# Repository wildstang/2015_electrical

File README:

This is the 2015 electrical repository. Branched commit.

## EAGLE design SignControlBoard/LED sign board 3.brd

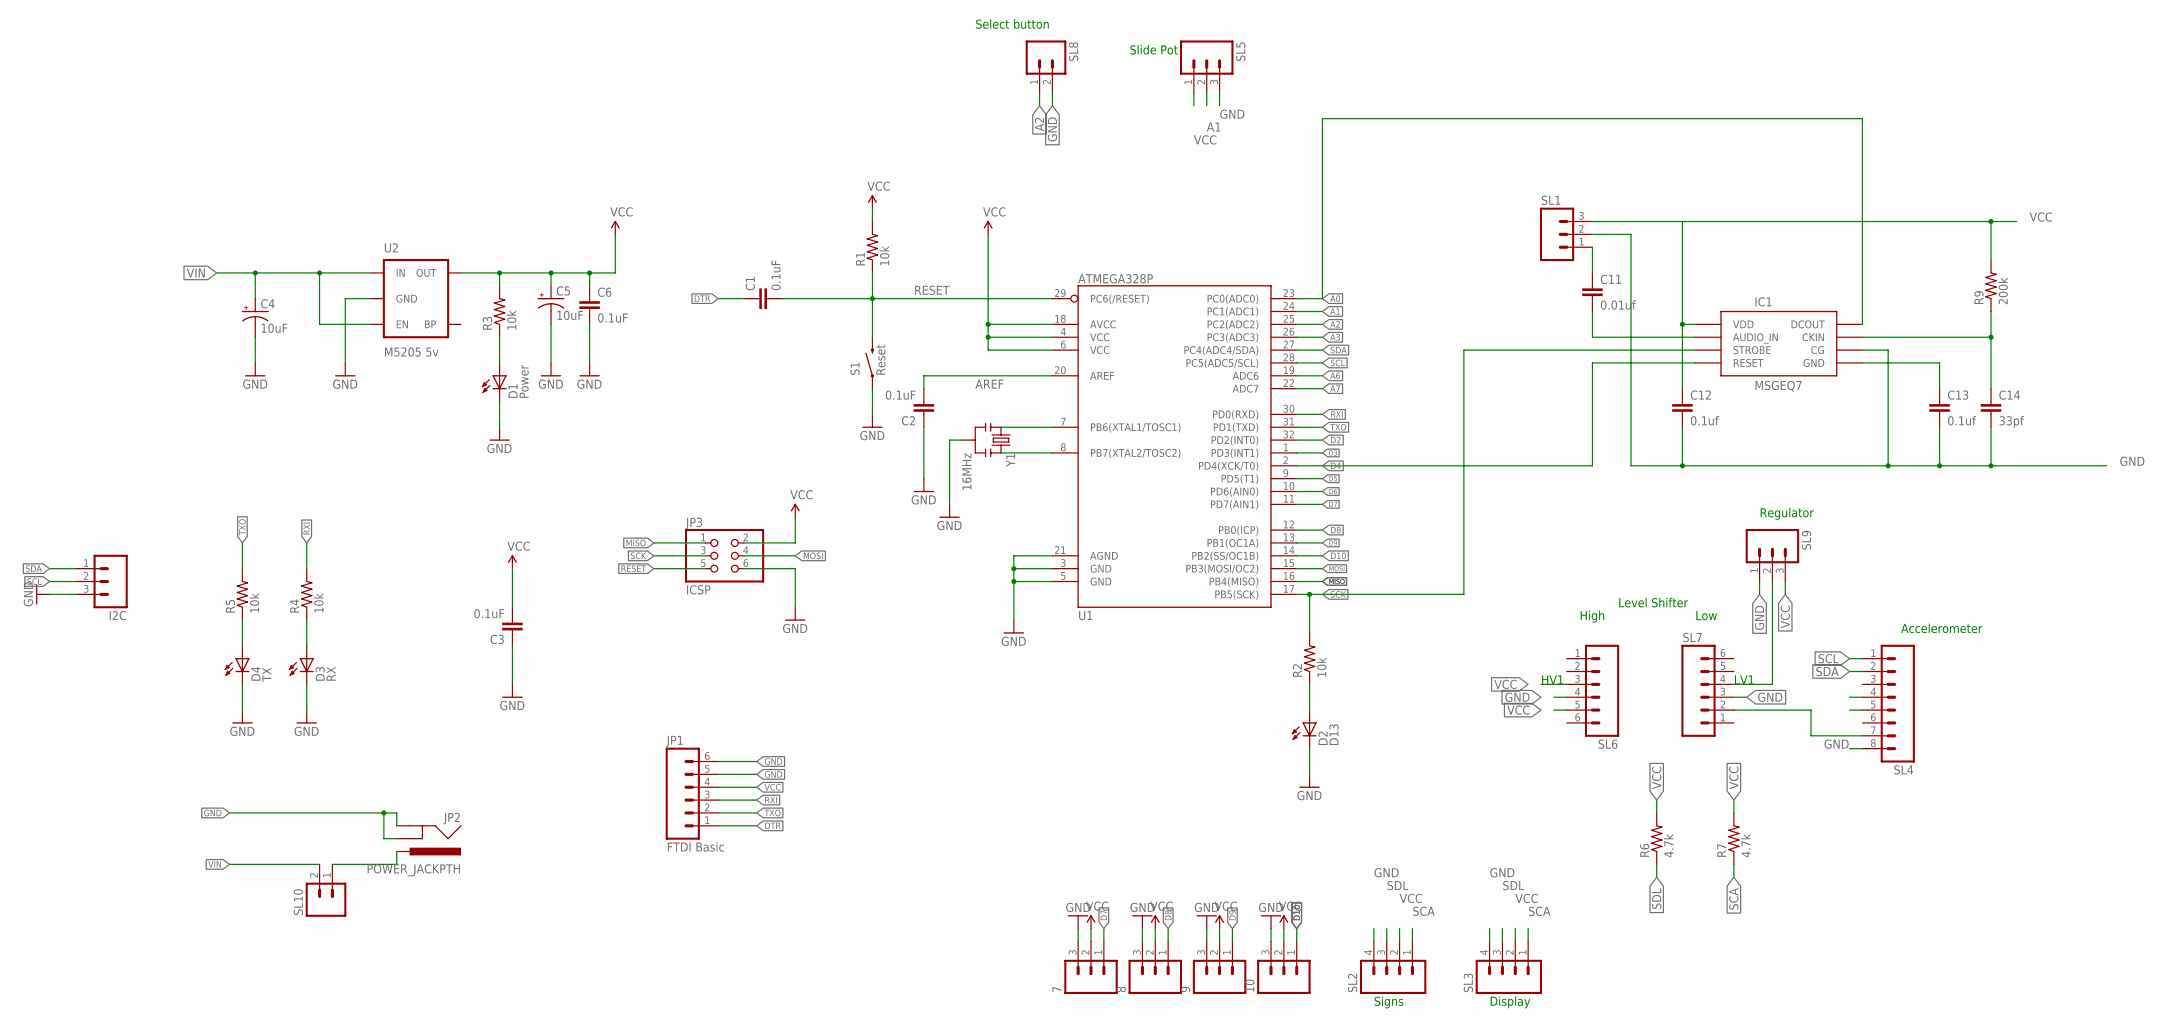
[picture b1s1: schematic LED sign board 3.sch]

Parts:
7, 8, 9, 10: M03PTH; 1X03
C1, C2, C3, C6: 0.1uF; 0603-CAP
C4, C5: 10uF; EIA3216
C11: 0.01uf; C0201
C12, C13: 0.1uf; C0201
C14: 33pf; C0201
D1: Power; LED-0603
D2: D13; LED-0603
D3: RX; LED-0603
D4: TX; LED-0603
I2C: M03PTH; 1X03
IC1: MSGEQ7DIL; DIL-08
JP1: FTDI Basic; 1X06
JP2: POWER_JACKPTH; POWER_JACK_PTH
JP3: ICSP; 2X03
R1, R2, R3, R4, R5: 10k; 0603-RES
R6, R7: 4.7k; 1206
R9: 200k; 1206
S1: Reset; TACTILE_SWITCH_SMD
SL1, SL5, SL9: M03; 03P
SL2, SL3: M04; 04P
SL4: M08; 08P
SL6, SL7: M06; 06P
SL8, SL10: M02; 02P
U1: ATMEGA328P; TQFP32-08
U2: M5205 5v; SOT23-5
Y1: 16MHz; RESONATOR-SMD

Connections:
A0: IC1.3 (DCOUT), U1.23 (PC0(ADC0))
A1: SL5.2, U1.24 (PC1(ADC1))
A2: SL8.1, U1.25 (PC2(ADC2))
A3: U1.26 (PC3(ADC3))
A6: U1.19 (ADC6)
A7: U1.22 (ADC7)
AREF: C2.2, U1.20 (AREF)
D2: U1.32 (PD2(INT0))
D3: U1.1 (PD3(INT1))
D4: IC1.7 (RESET), U1.2 (PD4(XCK/T0))
D5: U1.9 (PD5(T1))
D6: U1.10 (PD6(AIN0))
D7: 7.1, U1.11 (PD7(AIN1))
D8: 8.1, U1.12 (PB0(ICP))
D9: 9.1, U1.13 (PB1(OC1A))
D10: 10.1, U1.14 (PB2(SS/OC1B))
DTR: C1.1, JP1.1
GND: 7.3, 8.3, 9.3, 10.3, C2.1, C3.1, C4.C (-), C5.C (-), C6.2, C12.2, C13.2, C14.2, D1.C, D2.C, D3.C, D4.C, I2C.3, IC1.6 (CG), JP1.5, JP1.6, JP2.GND, JP2.GNDBREAK, JP3.6, S1.1, SL1.2, SL2.4, SL3.4, SL4.8, SL5.3, SL6.4, SL7.3, SL7.4, SL8.2, SL9.1, SL9.2, U1.3 (GND), U1.5 (GND), U1.21 (AGND), U2.2 (GND), Y1.2
MISO: JP3.1, U1.16 (PB4(MISO))
MOSI: JP3.4, U1.15 (PB3(MOSI/OC2))
unnamed: U1.7 (PB6(XTAL1/TOSC1)), Y1.1
unnamed: U1.8 (PB7(XTAL2/TOSC2)), Y1.3
unnamed: D1.A, R3.1
unnamed: D2.A, R2.1
unnamed: D3.A, R4.1
unnamed: D4.A, R5.1
unnamed: SL4.7, SL7.2
unnamed: JP2.PWR, SL10.1
unnamed: C11.1, SL1.1
unnamed: C11.2, IC1.5 (AUDIO_IN)
unnamed: C13.1, IC1.2 (GND)
unnamed: C14.1, IC1.8 (CKIN), R9.1
RESET: C1.2, JP3.5, R1.1, S1.3 (2), U1.29 (PC6(/RESET))
RXI: JP1.3, R4.2, U1.30 (PD0(RXD))
SCA: R7.1, SL2.1, SL3.1
SCK: IC1.4 (STROBE), JP3.3, R2.2, U1.17 (PB5(SCK))
SCL: I2C.2, SL4.1, U1.28 (PC5(ADC5/SCL))
SDA: I2C.1, SL4.2, U1.27 (PC4(ADC4/SDA))
SDL: R6.1, SL2.3, SL3.3
TXO: JP1.2, R5.2, U1.31 (PD1(TXD))
VCC: 7.2, 8.2, 9.2, 10.2, C3.2, C5.A (+), C6.1, C12.1, IC1.1 (VDD), JP1.4, JP3.2, R1.2, R3.2, R6.2, R7.2, R9.2, SL1.3, SL2.2, SL3.2, SL5.1, SL6.3, SL6.5, SL9.3, U1.4 (VCC), U1.6 (VCC), U1.18 (AVCC), U2.5 (OUT)
VIN: C4.A (+), SL10.2, U2.1 (IN), U2.3 (EN)

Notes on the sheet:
Accelerometer
Slide Pot
Display
Signs
Level Shifter
High
Low
Select button
Regulator
HV1
LV1

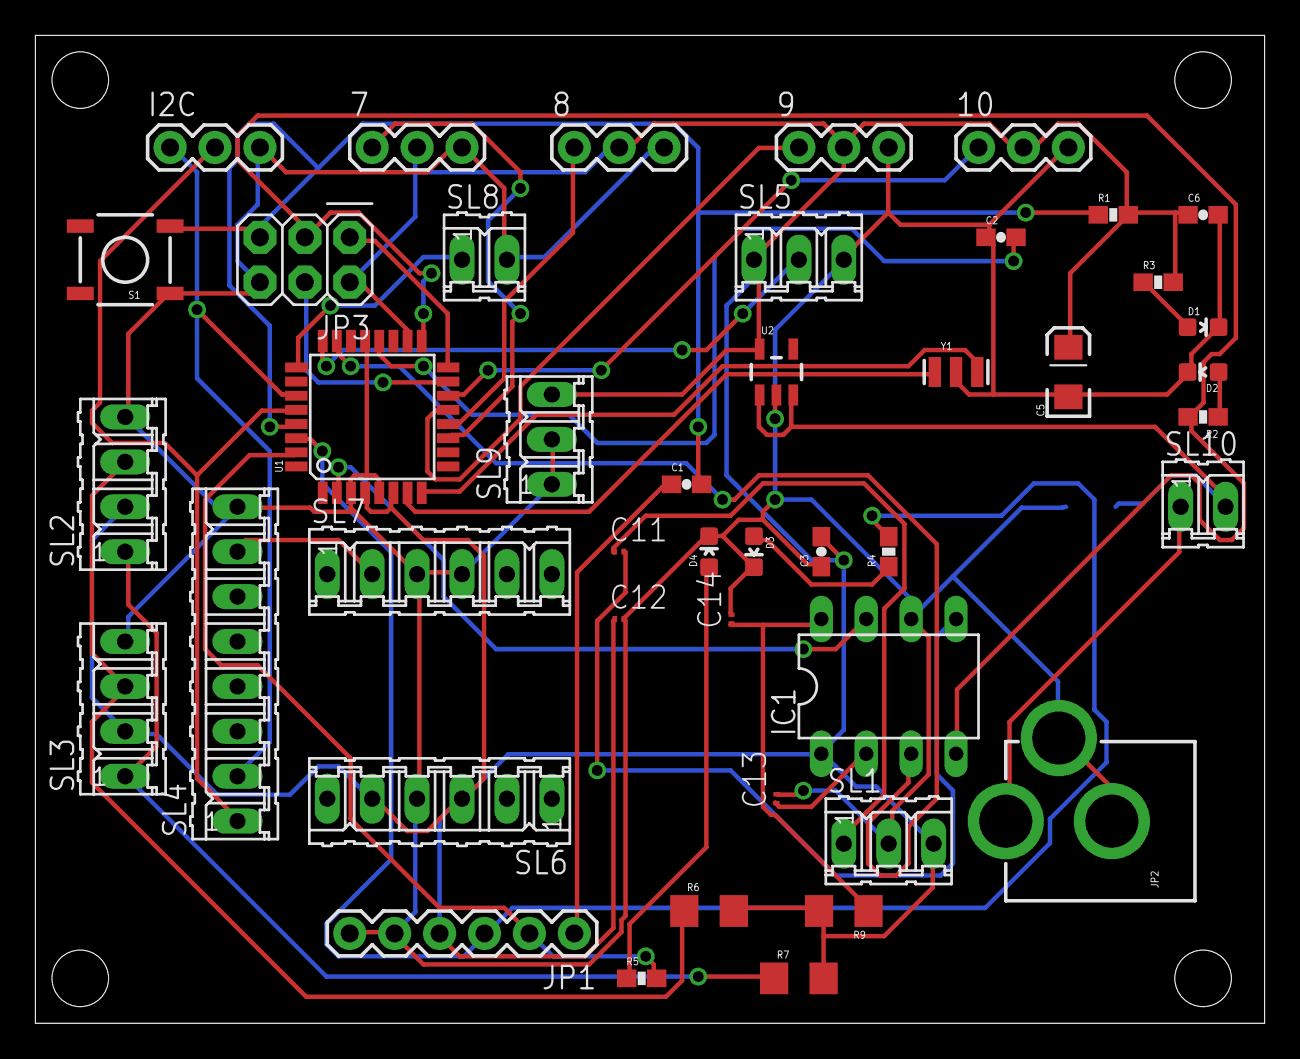
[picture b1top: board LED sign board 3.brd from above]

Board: 2 copper layers, 69.5 x 55.9 mm, 45 parts (1 on the bottom side), 35 nets.

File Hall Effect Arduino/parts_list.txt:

Partlist

Exported from Hall Effect Arduino.sch at 2/4/2015 12:22:48 PM

EAGLE Version 7.1.0 Copyright (c) 1988-2014 CadSoft

Assembly variant: 

Part     Value          Device                Package            Library                    Sheet

2                       M03PTH                1X03               SparkFun-Connectors        1
3                       M03PTH                1X03               SparkFun-Connectors        1
4                       M03PTH                1X03               SparkFun-Connectors        1
5                       M03PTH                1X03               SparkFun-Connectors        1
6                       M03PTH                1X03               SparkFun-Connectors        1
7                       M03PTH                1X03               SparkFun-Connectors        1
8                       M03PTH                1X03               SparkFun-Connectors        1
9                       M03PTH                1X03               SparkFun-Connectors        1
10                      M03PTH                1X03               SparkFun-Connectors        1
C1       0.1uF          CAP0603-CAP           0603-CAP           SparkFun-Passives          1
C2       0.1uF          CAP0603-CAP           0603-CAP           SparkFun-Passives          1
C3       0.1uF          CAP0603-CAP           0603-CAP           SparkFun-Passives          1
C4       10uF           CAP_POL1206           EIA3216            SparkFun-Passives          1
C5       10uF           CAP_POL1206           EIA3216            SparkFun-Passives          1
C6       0.1uF          CAP0603-CAP           0603-CAP           SparkFun-Passives          1
D1       Power          LED-RED0603           LED-0603           SparkFun-LED               1
D2       D13            LED-RED0603           LED-0603           SparkFun-LED               1
D3       RX             LED-GREEN0603         LED-0603           SparkFun-LED               1
D4       TX             LED-RED0603           LED-0603           SparkFun-LED               1
I2C                     M03PTH                1X03               SparkFun-Connectors        1
JP1      FTDI Basic     M06SIP                1X06               SparkFun-Connectors        1
JP3      ICSP           PINHD-2X3             2X03               SparkFun-Connectors        1
R1       10k            RESISTOR0603-RES      0603-RES           SparkFun-Passives          1
R2       10k            RESISTOR0603-RES      0603-RES           SparkFun-Passives          1
R3       10k            RESISTOR0603-RES      0603-RES           SparkFun-Passives          1
R4       10k            RESISTOR0603-RES      0603-RES           SparkFun-Passives          1
R5       10k            RESISTOR0603-RES      0603-RES           SparkFun-Passives          1
S1       Reset          SWITCH-MOMENTARY-2SMD TACTILE_SWITCH_SMD SparkFun-Electromechanical 1
U$1      LSF-SMT        LSF-SMT               LSF-SMT            LSF-SMT                    1
U1       ATMEGA328P     ATMEGA328_SMT         TQFP32-08          SparkFun-DigitalIC         1
U2       M5205 5v       MIC52055V             SOT23-5            SparkFun-PowerIC           1
Y1       16MHz          RESONATOR16MHZ        RESONATOR-SMD      SparkFun-FreqCtrl          1

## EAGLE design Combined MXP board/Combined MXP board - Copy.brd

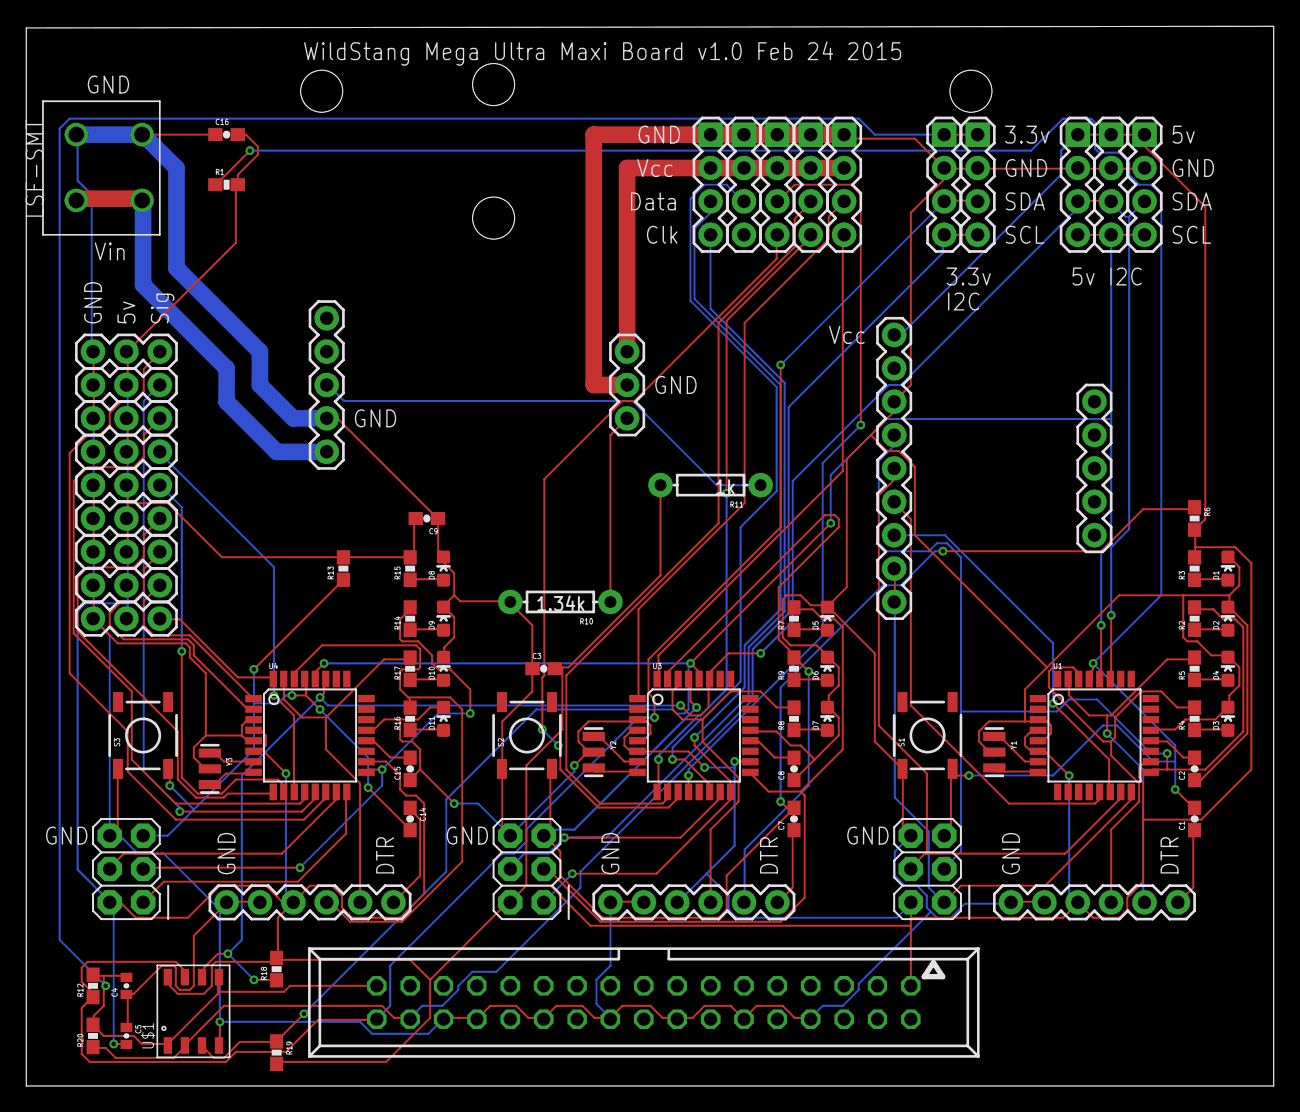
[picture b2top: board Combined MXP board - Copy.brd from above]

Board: 2 copper layers, 94.9 x 80.6 mm, 83 parts (0 on the bottom side), 70 nets.

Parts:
2, 3, 4, 5, 6, 7, 8, 9, 10: 1X03
C1, C2, C3, C7, C8, C9, C14, C15, C16: 0.1uF; 0603-CAP
C4, C5: 0402-CAP
D1, D8: Power; LED-0603
D2, D5, D9: D13; LED-0603
D3, D7, D11: RX; LED-0603
D4, D6, D10: TX; LED-0603
JP1, JP10, JP21: FTDI Basic; 1X06
JP2, JP4, JP5, JP6, JP9, JP15, JP16, JP17, JP18, JP19: 1X04
JP3, JP11, JP22: ICSP; 2X03
JP7: M09; 1X09
JP8, JP13: 1X05
JP20: 1X03
R1, R2, R3, R4, R5, R6, R7, R8, R9, R12, R13, R14, R15, R16, R17, R18, R19, R20: 10k; 0603-RES
R10: 1.34k; AXIAL-0.3
R11: 1k; AXIAL-0.3
S1, S2, S3: Reset; TACTILE_SWITCH_SMD
U1, U3, U4: ATMEGA328P; TQFP32-08
U$1: PCA9512A
U$2: LSF-SMT
X1: 057-034-1
Y1, Y2, Y3: 16MHz; RESONATOR-SMD

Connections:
AREF: C2.2, U1.20
D9: JP7.6, U1.13
D10: JP7.7, U1.14
DTR: C1.1, JP1.1
GND: 2.3, 3.3, 4.3, 5.3, 6.3, 7.3, 8.3, 9.3, 10.3, C2.1, C3.1, C4.1, C5.1, C8.1, C9.1, C15.1, C16.1, D1.C, D2.C, D3.C, D4.C, D5.C, D6.C, D7.C, D8.C, D9.C, D10.C, D11.C, JP1.5, JP1.6, JP2.2, JP3.6, JP4.2, JP5.2, JP6.2, JP7.3, JP9.2, JP10.5, JP10.6, JP11.6, JP13.4, JP15.1, JP16.1, JP17.1, JP18.1, JP19.1, JP20.2, JP21.5, JP21.6, JP22.6, R10.P$2, S1.1, S2.1, S3.1, U1.3, U1.5, U1.21, U3.3, U3.5, U3.21, U4.3, U4.5, U4.21, U$1.GND, U$2.1, U$2.1-2, X1.8, X1.12, X1.16, X1.20, X1.24, X1.28, X1.30, Y1.2, Y2.2, Y3.2
HE-AREF: C15.2, U4.20
HE-D2: 2.1, U4.32
HE-D3: 3.1, U4.1
HE-D4: 4.1, U4.2
HE-D5: 5.1, U4.9
HE-D6: 6.1, U4.10
HE-D7: 7.1, U4.11
HE-D8: 8.1, U4.12
HE-D9: 9.1, U4.13
HE-D10: 10.1, U4.14
HE-DTR: C14.1, JP21.1
HE-MISO: JP22.1, U4.16
HE-MOSI: JP22.4, U4.15
HE-RESET: C14.2, JP22.5, R13.1, S3.3, U4.29
HE-RXI: JP21.3, R16.2, U4.30
HE-SCK: JP22.3, R14.2, U4.17
HE-TXO: JP21.2, R17.2, U4.31
LED-AREF: C8.2, U3.20
LED-D2: JP15.4, U3.32
LED-D3: JP15.3, U3.1
LED-D5: JP16.4, U3.9
LED-D6: JP16.3, U3.10
LED-D7: JP17.4, U3.11
LED-D8: JP17.3, U3.12
LED-D10: JP18.3, U3.14
LED-DTR: C7.1, JP10.1
LED-MISO: JP11.1, JP19.3, U3.16
LED-MOSI: JP11.4, JP19.4, U3.15
LED-RESET: C7.2, JP11.5, R6.1, S2.3, U3.29
LED-RXI: JP10.3, R8.2, U3.30
LED-SCK: JP11.3, R7.2, U3.17
LED-TXO: JP10.2, R9.2, U3.31
LED-VCC: JP15.2, JP16.2, JP17.2, JP18.2, JP19.2, JP20.1
MISO: JP3.1, JP7.8, JP7.9, U1.16
MOSI: JP3.4, JP7.5, U1.15
unnamed: U1.7, Y1.1
unnamed: U1.8, Y1.3
unnamed: D1.A, R3.1
unnamed: D2.A, R2.1
unnamed: D3.A, R4.1
unnamed: D4.A, R5.1
unnamed: U3.7, Y2.1
unnamed: U3.8, Y2.3
unnamed: D5.A, R7.1
unnamed: D6.A, R9.1
unnamed: D7.A, R8.1
unnamed: JP20.3, R10.P$1
unnamed: JP13.3, R11.P$1
unnamed: U4.7, Y3.1
unnamed: U4.8, Y3.3
unnamed: D8.A, R15.1
unnamed: D9.A, R14.1
unnamed: D10.A, R17.1
unnamed: D11.A, R16.1
RESET: C1.2, JP3.5, R1.1, S1.3, U1.29
RXI: JP1.3, R4.2, U1.30
SCK: JP3.3, JP7.4, R2.2, U1.17
SCL: JP2.4, JP6.4, JP9.4, R19.1, U1.28, U3.28, U4.28, U$1.SCLIN
SCL3.3: JP4.4, JP5.4, R20.1, U$1.SCLOUT, X1.32
SDA: JP2.3, JP6.3, JP9.3, R18.1, U1.27, U3.27, U4.27, U$1.SDAIN
SDA3.3: JP4.3, JP5.3, R12.1, U$1.SDAOUT, X1.34
TXO: JP1.2, R5.2, U1.31
VCC: 2.2, 3.2, 4.2, 5.2, 6.2, 7.2, 8.2, 9.2, 10.2, C3.2, C5.2, C9.2, C16.2, JP1.4, JP2.1, JP3.2, JP6.1, JP7.1, JP9.1, JP10.4, JP11.2, JP21.4, JP22.2, R1.2, R3.2, R6.2, R11.P$2, R13.2, R15.2, R18.2, R19.2, U1.4, U1.6, U1.18, U3.4, U3.6, U3.18, U4.4, U4.6, U4.18, U$1.VCCH, X1.1
VCC3.3: C4.2, JP4.1, JP5.1, R12.2, R20.2, U$1.ACC, U$1.VCCL, X1.33
VIN: JP13.5, U$2.2, U$2.2-2

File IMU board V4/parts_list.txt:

Partlist

Exported from IMU board V4.sch at 2/4/2015 12:23:27 PM

EAGLE Version 7.1.0 Copyright (c) 1988-2014 CadSoft

Assembly variant: 

Part     Value          Device                Package            Library                    Sheet

C1       0.1uF          CAP0603-CAP           0603-CAP           SparkFun-Passives          1
C2       0.1uF          CAP0603-CAP           0603-CAP           SparkFun-Passives          1
C3       0.1uF          CAP0603-CAP           0603-CAP           SparkFun-Passives          1
C4       10uF           CAP_POL1206           EIA3216            SparkFun-Passives          1
C5       10uF           CAP_POL1206           EIA3216            SparkFun-Passives          1
C6       0.1uF          CAP0603-CAP           0603-CAP           SparkFun-Passives          1
D1       Power          LED-RED0603           LED-0603           SparkFun-LED               1
D2       D13            LED-RED0603           LED-0603           SparkFun-LED               1
D3       RX             LED-GREEN0603         LED-0603           SparkFun-LED               1
D4       TX             LED-RED0603           LED-0603           SparkFun-LED               1
I2C                     M03PTH                1X03               SparkFun-Connectors        1
JP1      FTDI Basic     M06SIP                1X06               SparkFun-Connectors        1
JP2                     M04PTH                1X04               SparkFun-Connectors        1
JP3      ICSP           PINHD-2X3             2X03               SparkFun-Connectors        1
JP4                     M04PTH                1X04               SparkFun-Connectors        1
JP5                     M04PTH                1X04               SparkFun-Connectors        1
JP6                     M04PTH                1X04               SparkFun-Connectors        1
JP7      M09            M09                   1X09               SparkFun-Connectors        1
JP8                     M05PTH                1X05               SparkFun-Connectors        1
JP9                     M04PTH                1X04               SparkFun-Connectors        1
R1       10k            RESISTOR0603-RES      0603-RES           SparkFun-Passives          1
R2       10k            RESISTOR0603-RES      0603-RES           SparkFun-Passives          1
R3       10k            RESISTOR0603-RES      0603-RES           SparkFun-Passives          1
R4       10k            RESISTOR0603-RES      0603-RES           SparkFun-Passives          1
R5       10k            RESISTOR0603-RES      0603-RES           SparkFun-Passives          1
S1       Reset          SWITCH-MOMENTARY-2SMD TACTILE_SWITCH_SMD SparkFun-Electromechanical 1
U$1      LSF-SMT        LSF-SMT               LSF-SMT            LSF-SMT                    1
U1       ATMEGA328P     ATMEGA328_SMT         TQFP32-08          SparkFun-DigitalIC         1
U2       M5205 5v       MIC52055V             SOT23-5            SparkFun-PowerIC           1
Y1       16MHz          RESONATOR16MHZ        RESONATOR-SMD      SparkFun-FreqCtrl          1

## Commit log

2015-01-24 Initial Commit.
2015-01-24 testing git gui
2015-01-24 test commit #2
2015-01-25 test commit with smart git
2015-01-25 this is a branched commit.
2015-01-25 README edited online with Bitbucket
2015-01-29 Initial release of boards
2015-01-29 Initial 2015 Robot LED code
2015-01-30 I made a change
2015-01-30 Arduino board for hall effect sensors
2015-01-30 Deleted!
2015-01-30 Initial Adruino board
2015-01-30 Deleted files
2015-01-30 Added basic board
2015-01-30 Updated with header pins
2015-02-02 Updated with final board for production.
2015-02-06 Added parts list for each board
2015-02-07 Working to 1s place. Now for decimals...
2015-02-15 Hall effect sensor test code and board code.
2015-02-27 Combined Mega Ultra Maxi Board. Contains the IMU board, LED board and Hall Effect sensor input board.
2015-03-07 Updated for sensor hold time
2015-04-18 Updated core code for LED integration

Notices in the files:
parts and their libraries:
SparkFun-Connectors: Licensing: Creative Commons ShareAlike 4.0 International - https://creativecommons.org/licenses/by-sa/4.0
